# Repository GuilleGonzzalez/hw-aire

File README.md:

# Aire

## Description

'Aire' is a PCB designed to control a fan with three relays and automatize it with [Home Assistant](https://www.home-assistant.io/).

Firmware used in this device is [fw-aire](https://github.com/GuilleGonzzalez/fw-aire), a custom made firmware implemented using [Arduino Home Assistant](https://github.com/dawidchyrzynski/arduino-home-assistant/tree/main) Arduino library ([docs](https://dawidchyrzynski.github.io/arduino-home-assistant/)).

## Power supply

The board is powered with a 230VAC power supply.

## Microprocessor

Espressif [ESP32-S2-SOLO](https://www.espressif.com/en/products/modules) module (NRND).

## Environmental sensing

The board has enviromental sensors to measure temperature, humidity and atmospheric pressure:

### Temperature and humidity sensor

* Sensirion [SHT40](https://sensirion.com/products/catalog/SHT40).

### Pressure sensor

* Bosch [BMP581](https://www.bosch-sensortec.com/products/environmental-sensors/pressure-sensors/bmp581/).

## LEDs and buttons

//TODO: review

The device has three LEDs for showing the status to the user.
* A power LED (LED1): shows the status of the fan.
* A general device LED (LED2): shows the status of the general air machine.
* A LED reserved for the future.

The device has a button for flash the firmware in the microcontroller, and is also used for the user.

The board has an external connector available for the three LEDs and the button.

## Pin assignment

| PIN     | Func    |
| ------- | ------- |
| TODO    | TODO    |

## Enclosure (WIP)
* Custom made in [Fusion 360](https://www.autodesk.es/products/fusion-360/overview).

# Changelog
All notable changes to this project will be documented in this section.

The format is based on [Keep a Changelog](https://keepachangelog.com/en/1.0.0/)

## [3.0.0] - 2024-04-24
### Fix
- Change microcontroller for more GPIOs
- Remove IO expander
- SMD LEDs
- Change connectors to JST
- Add external connector
- Envirometal sensors with cutouts for avoid hot
## [2.0.0] - 2023-09-04
### Added
- First stable release in this repository

[Unreleased]: https://github.com/GuilleGonzzalez/hw-aire
[2.0.0]: https://github.com/GuilleGonzzalez/hw-aire/releases/tag/v2.0.0
[3.0.0]: https://github.com/GuilleGonzzalez/hw-aire/releases/tag/v3.0.0

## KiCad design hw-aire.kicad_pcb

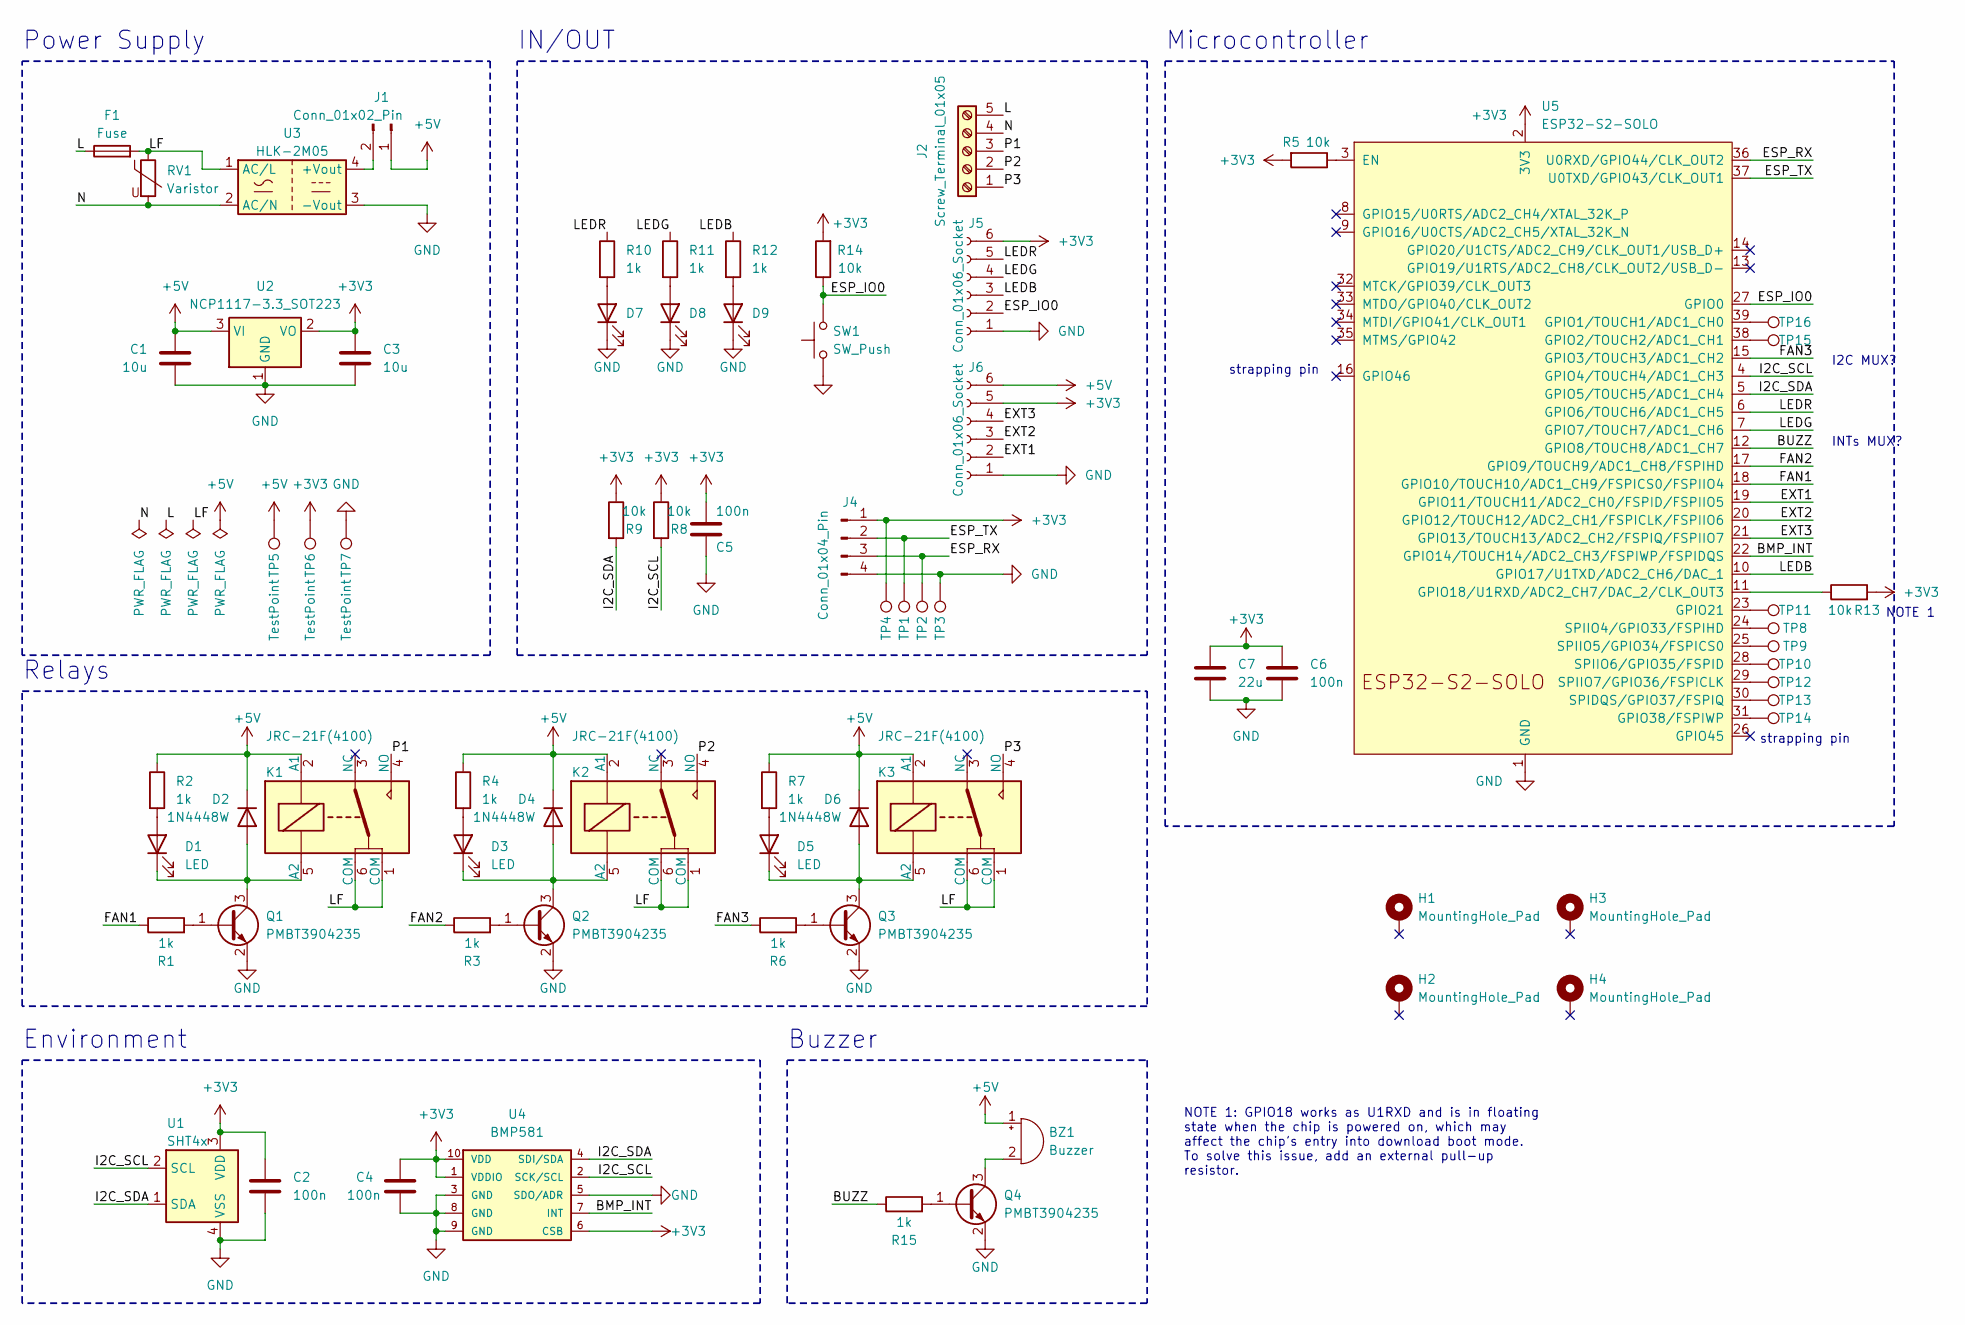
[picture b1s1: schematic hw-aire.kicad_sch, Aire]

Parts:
BZ1: Buzzer; Buzzer_12x9.5RM7.6
C1, C3: 10u; C_1206_3216Metric
C2, C4, C5, C6: 100n; C_0402_1005Metric
C7: 22u; C_0805_2012Metric
D1, D3, D5, D7, D8, D9: LED; LED_0603_1608Metric
D2, D4, D6: 1N4448W; D_SOD-323
F1: Fuse; Fuse_2512_6332Metric
H1, H2, H3, H4: MountingHole_Pad; MountingHole_3.2mm_M3_Pad_TopBottom
J1: Conn_01x02_Pin; PinHeader_1x02_P2.54mm_Vertical
J2: Screw_Terminal_01x05; TerminalBlock_Phoenix_MKDS-1,5-5-5.08_1x05_P5.08mm_Horizont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
J4: Conn_01x04_Pin; PinHeaderOffset_1x04_P2.54mm_Vertical
J5, J6: Conn_01x06_Socket; JST_XH_B6B-XH-A_1x06_P2.50mm_Vertical
K1, K2, K3: JRC-21F(4100)
Q1, Q2, Q3, Q4: PMBT3904235; SOT-23; Manufacturer_PN PMBT3904,235
R1, R2, R3, R4, R6, R7, R10, R11, R12, R15: 1k; R_0402_1005Metric
R5, R8, R9, R13, R14: 10k; R_0402_1005Metric
RV1: Varistor; RV_Disc_D12mm_W4.5mm_P7.5mm
SW1: SW_Push; SW_SPST_PTS810
TP1, TP2, TP3, TP4, TP5, TP6, TP7, TP8, TP9, TP10, TP11, TP12, TP13, TP14, TP15, TP16: TestPoint; TestPoint_Pad_D1.5mm
U1: SHT4x
U2: NCP1117-3.3_SOT223; SOT-223-3_TabPin2
U3: HLK-2M05
U4: BMP581; Manufacturer PN BMP581
U5: ESP32-S2-SOLO

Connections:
+3V3: C2.1, C3.1, C4.1, C5.1, C6.1, C7.1, J4.1, J5.6, J6.5, R5.2, R8.1, R9.1, R13.2, R14.2, TP4.1, TP6.1, U1.3 (VDD), U2.2 (VO), U4.1 (VDDIO), U4.6 (CSB), U4.10 (VDD), U5.2 (3V3)
+5V: BZ1.1 (-), C1.1, D2.1 (K), D4.1 (K), D6.1 (K), J1.1, J6.6, K1.2 (A1), K2.2 (A1), K3.2 (A1), R2.1, R4.1, R7.1, TP5.1, U2.3 (VI)
/BMP_INT: U4.7 (INT), U5.22 (GPIO14/TOUCH14/ADC2_CH3/FSPIWP/FSPIDQS)
/BUZZ: R15.1, U5.12 (GPIO8/TOUCH8/ADC1_CH7)
/ESP_IO0: J5.2, R14.1, SW1.2, U5.27 (GPIO0)
/ESP_RX: J4.3, TP2.1, U5.36 (U0RXD/GPIO44/CLK_OUT2)
/ESP_TX: J4.2, TP1.1, U5.37 (U0TXD/GPIO43/CLK_OUT1)
/EXT1: J6.2, U5.19 (GPIO11/TOUCH11/ADC2_CH0/FSPID/FSPIIO5)
/EXT2: J6.3, U5.20 (GPIO12/TOUCH12/ADC2_CH1/FSPICLK/FSPIIO6)
/EXT3: J6.4, U5.21 (GPIO13/TOUCH13/ADC2_CH2/FSPIQ/FSPIIO7)
/FAN1: R1.1, U5.18 (GPIO10/TOUCH10/ADC1_CH9/FSPICS0/FSPIIO4)
/FAN2: R3.1, U5.17 (GPIO9/TOUCH9/ADC1_CH8/FSPIHD)
/FAN3: R6.1, U5.15 (GPIO3/TOUCH3/ADC1_CH2)
/I2C_SCL: R8.2, U1.2 (SCL), U4.2 (SCK/SCL), U5.4 (GPIO4/TOUCH4/ADC1_CH3)
/I2C_SDA: R9.2, U1.1 (SDA), U4.4 (SDI/SDA), U5.5 (GPIO5/TOUCH5/ADC1_CH4)
/L: F1.1, J2.5
/LEDB: J5.3, R12.1, U5.10 (GPIO17/U1TXD/ADC2_CH6/DAC_1)
/LEDG: J5.4, R11.1, U5.7 (GPIO7/TOUCH7/ADC1_CH6)
/LEDR: J5.5, R10.1, U5.6 (GPIO6/TOUCH6/ADC1_CH5)
/LF: F1.2, K1.1 (COM), K1.6 (COM), K2.1 (COM), K2.6 (COM), K3.1 (COM), K3.6 (COM), RV1.1, U3.1 (AC/L)
/N: J2.4, RV1.2, U3.2 (AC/N)
/P1: J2.3, K1.4 (NO)
/P2: J2.2, K2.4 (NO)
/P3: J2.1, K3.4 (NO)
GND: C1.2, C2.2, C3.2, C4.2, C5.2, C6.2, C7.2, D7.1 (K), D8.1 (K), D9.1 (K), J4.4, J5.1, J6.1, Q1.2, Q2.2, Q3.2, Q4.2, SW1.1, TP3.1, TP7.1, U1.4 (VSS), U2.1 (GND), U3.3 (-Vout), U4.3 (GND), U4.5 (SDO/ADR), U4.8 (GND), U4.9 (GND), U5.1 (GND), U5.40 (GND), U5.41 (GND)
unnamed: BZ1.2 (+), Q4.3
unnamed: D1.2 (A), R2.2
unnamed: D1.1 (K), D2.2 (A), K1.5 (A2), Q1.3
unnamed: D3.2 (A), R4.2
unnamed: D3.1 (K), D4.2 (A), K2.5 (A2), Q2.3
unnamed: D5.2 (A), R7.2
unnamed: D5.1 (K), D6.2 (A), K3.5 (A2), Q3.3
unnamed: D7.2 (A), R10.2
unnamed: D8.2 (A), R11.2
unnamed: D9.2 (A), R12.2
unnamed: J1.2, U3.4 (+Vout)
unnamed: Q1.1, R1.2
unnamed: Q2.1, R3.2
unnamed: Q3.1, R6.2
unnamed: Q4.1, R15.2
unnamed: R5.1, U5.3 (EN)
unnamed: TP16.1, U5.39 (GPIO1/TOUCH1/ADC1_CH0)
unnamed: TP15.1, U5.38 (GPIO2/TOUCH2/ADC1_CH1)
unnamed: R13.1, U5.11 (GPIO18/U1RXD/ADC2_CH7/DAC_2/CLK_OUT3)
unnamed: TP11.1, U5.23 (GPIO21)
unnamed: TP14.1, U5.31 (GPIO38/FSPIWP)
unnamed: TP13.1, U5.30 (SPIDQS/GPIO37/FSPIQ)
unnamed: TP8.1, U5.24 (SPIIO4/GPIO33/FSPIHD)
unnamed: TP9.1, U5.25 (SPIIO5/GPIO34/FSPICS0)
unnamed: TP10.1, U5.28 (SPIIO6/GPIO35/FSPID)
unnamed: TP12.1, U5.29 (SPIIO7/GPIO36/FSPICLK)

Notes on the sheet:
Buzzer
strapping pin
INTs MUX?
Relays
Power Supply
NOTE 1: GPIO18 works as U1RXD and is in floating state when the chip is powered on, which may affect the chip’s entry into download boot mode. To solve this issue, add an external pull-up resistor.
Environment
NOTE 1
I2C MUX?
Microcontroller
IN/OUT

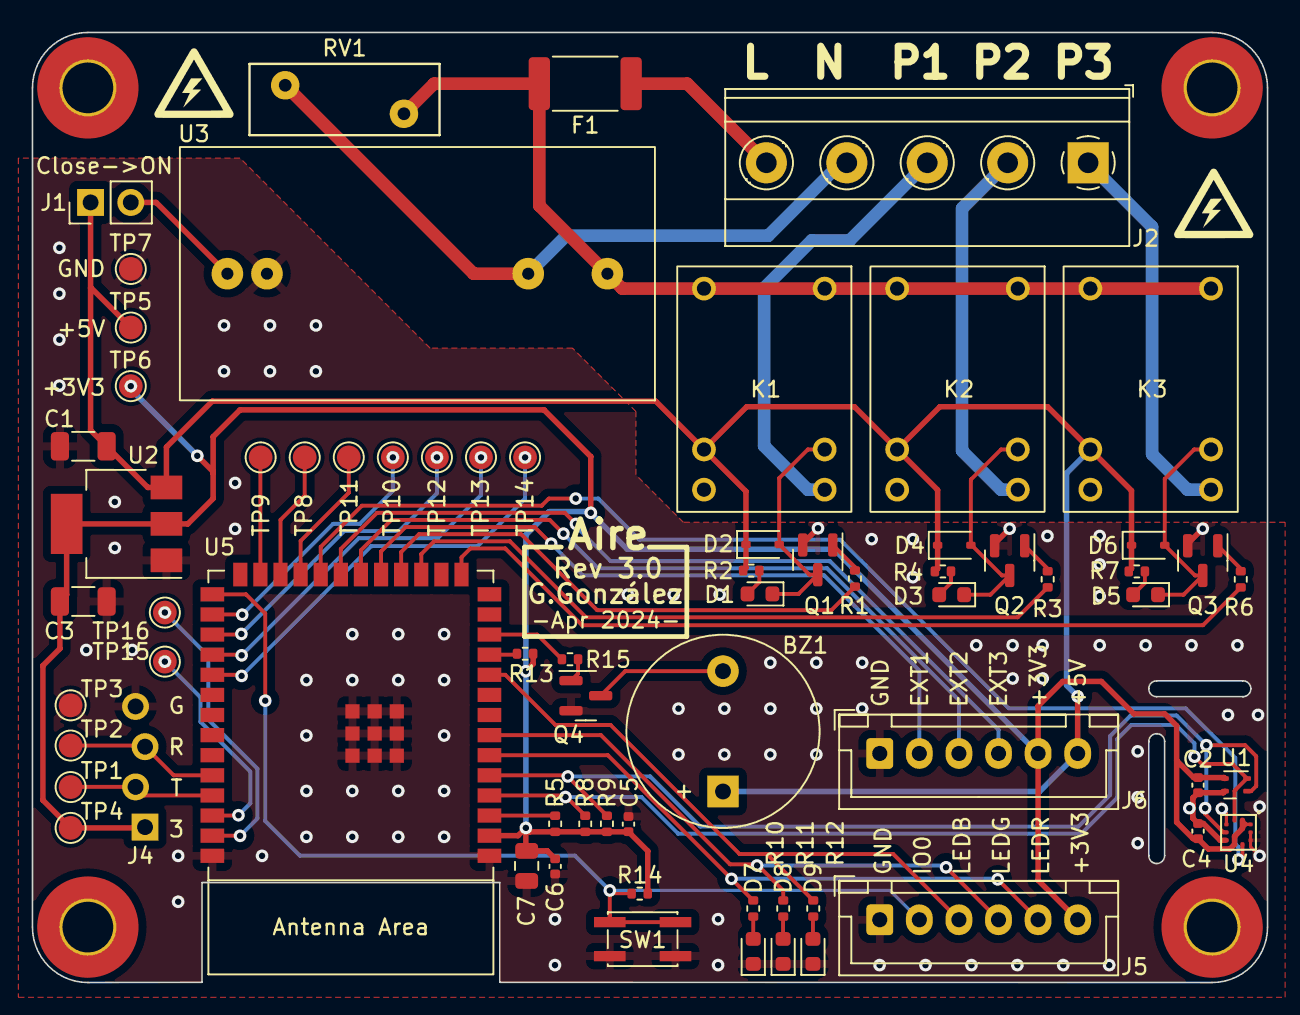
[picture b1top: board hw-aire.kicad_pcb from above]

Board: 2 copper layers, 78.0 x 60.0 mm, 72 parts (0 on the bottom side), 51 nets.

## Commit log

2023-08-29 Work in schematic
2023-08-29 All components linked with fp in schematic
2023-08-30 Update schematic
2023-09-02 Sch changes, add net classes and first placement
2023-09-03 Finish routing and serigraphy. Ready to review
2023-09-04 New revision, add IO expander and fix I2C GPIOs
2023-09-04 Revision 2.0
2024-04-17 Add connector label SVG
2024-04-17 Start changing SCH for rev 3.0
    - Change ESP8266 to ESP32-SOLO
    - Change to cold relays
2024-04-24 Finish PCB rev 3.0
2024-04-24 Review README
2024-04-24 Revision 3.0
2024-04-24 README minor fix
